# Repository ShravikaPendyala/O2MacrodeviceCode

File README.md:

Uploaded all my files to GitHub and am set up to commit any changes from local without uploading all files again and again like in the old O2Macrodevice repo.
files in the main branch are rarely edited, refer to SrcCode and Middlewares branches for any updates/changes in code!

Project on system: \git\O2MacrodeviceCode\NFC08A1_PollingTagDetectNDEF

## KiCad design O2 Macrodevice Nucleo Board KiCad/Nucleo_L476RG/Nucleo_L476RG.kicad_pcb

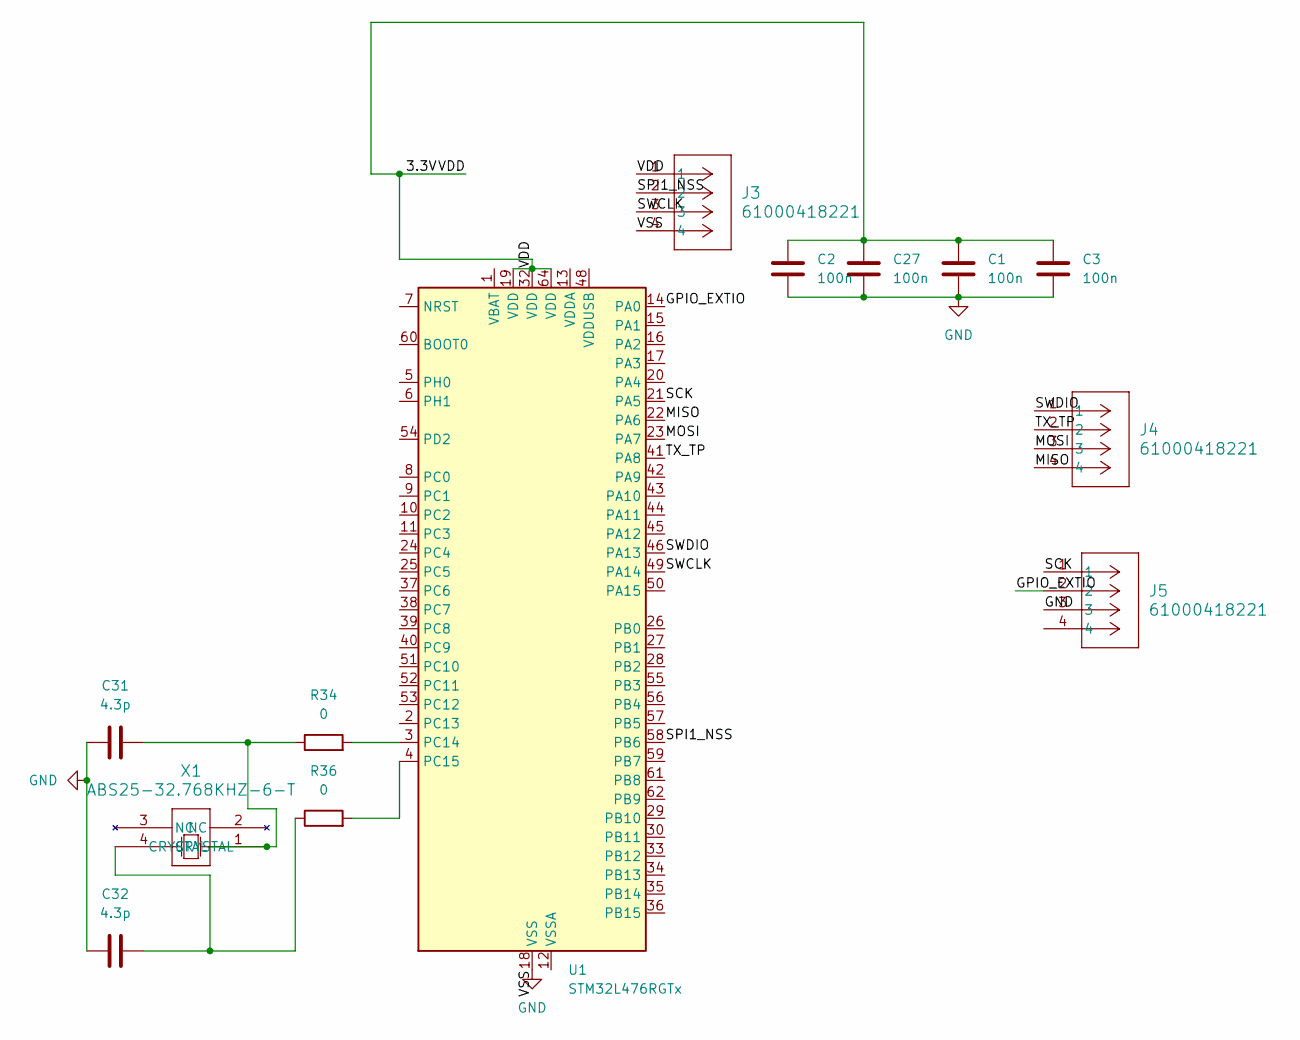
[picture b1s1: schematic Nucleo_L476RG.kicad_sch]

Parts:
C1, C2, C3, C27: 100n; C_0402_1005Metric_Pad0.74x0.62mm_HandSolder
C31, C32: 4.3p; C_0402_1005Metric_Pad0.74x0.62mm_HandSolder
J3, J4, J5: 61000418221; 61000418221_WRE
R34, R36: 0; R_0402_1005Metric_Pad0.72x0.64mm_HandSolder
U1: STM32L476RGTx; LQFP-64_10x10mm_P0.5mm
X1: ABS25-32.768KHZ-6-T; X_ABS25_ABR

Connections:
/<NO NET>: C1.2, C2.2, C3.2, C27.2, J3.1, U1.19 (VDD), U1.32 (VDD), U1.64 (VDD)
/GPIO_EXTIO: J5.2, U1.14 (PA0)
/MISO: J4.4, U1.22 (PA6)
/MOSI: J4.3, U1.23 (PA7)
/SCK: J5.1, U1.21 (PA5)
/SPI1_NSS: J3.2, U1.58 (PB6)
/SWCLK: J3.3, U1.49 (PA14)
/SWDIO: J4.1, U1.46 (PA13)
/TX_TP: J4.2, U1.41 (PA8)
GND: C1.1, C2.1, C3.1, C27.1, C31.1, C32.1, J3.4, J5.3, U1.18 (VSS), U1.31 (VSS), U1.47 (VSS), U1.63 (VSS)
unnamed: C31.2, R34.1, X1.1 (CRYSTAL)
unnamed: C32.2, R36.1, X1.4 (CRYSTAL)
unnamed: R34.2, U1.3 (PC14)
unnamed: R36.2, U1.4 (PC15)

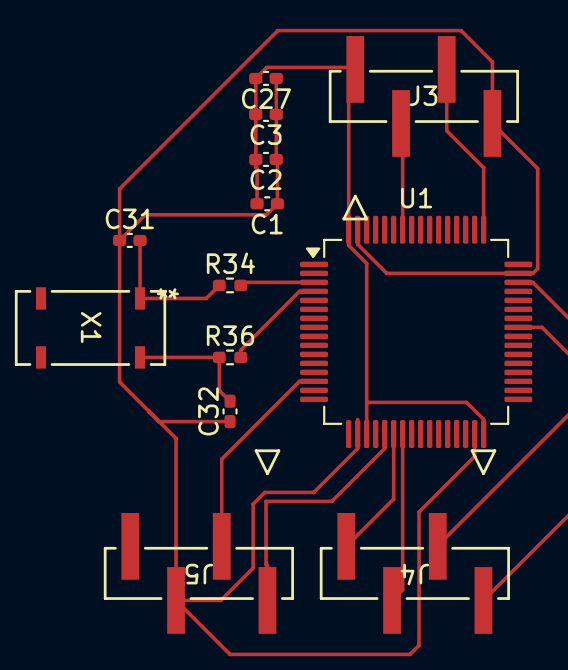
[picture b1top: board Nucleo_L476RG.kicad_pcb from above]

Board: 2 copper layers, 13 parts (0 on the bottom side), 14 nets.

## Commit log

2024-07-27 files from git/O2MacrodeviceCode/NFC08...
2024-07-28 uploading the important code from Src in git/O2MacrodeviceCode/Src
2024-07-28 uploading all the files in c:/middlewares
2024-07-28 testing update to code from middlewares
2024-07-28 updated NFC and Nucleo boards with new SMD header connectors
2024-07-28 some random untracked file?
